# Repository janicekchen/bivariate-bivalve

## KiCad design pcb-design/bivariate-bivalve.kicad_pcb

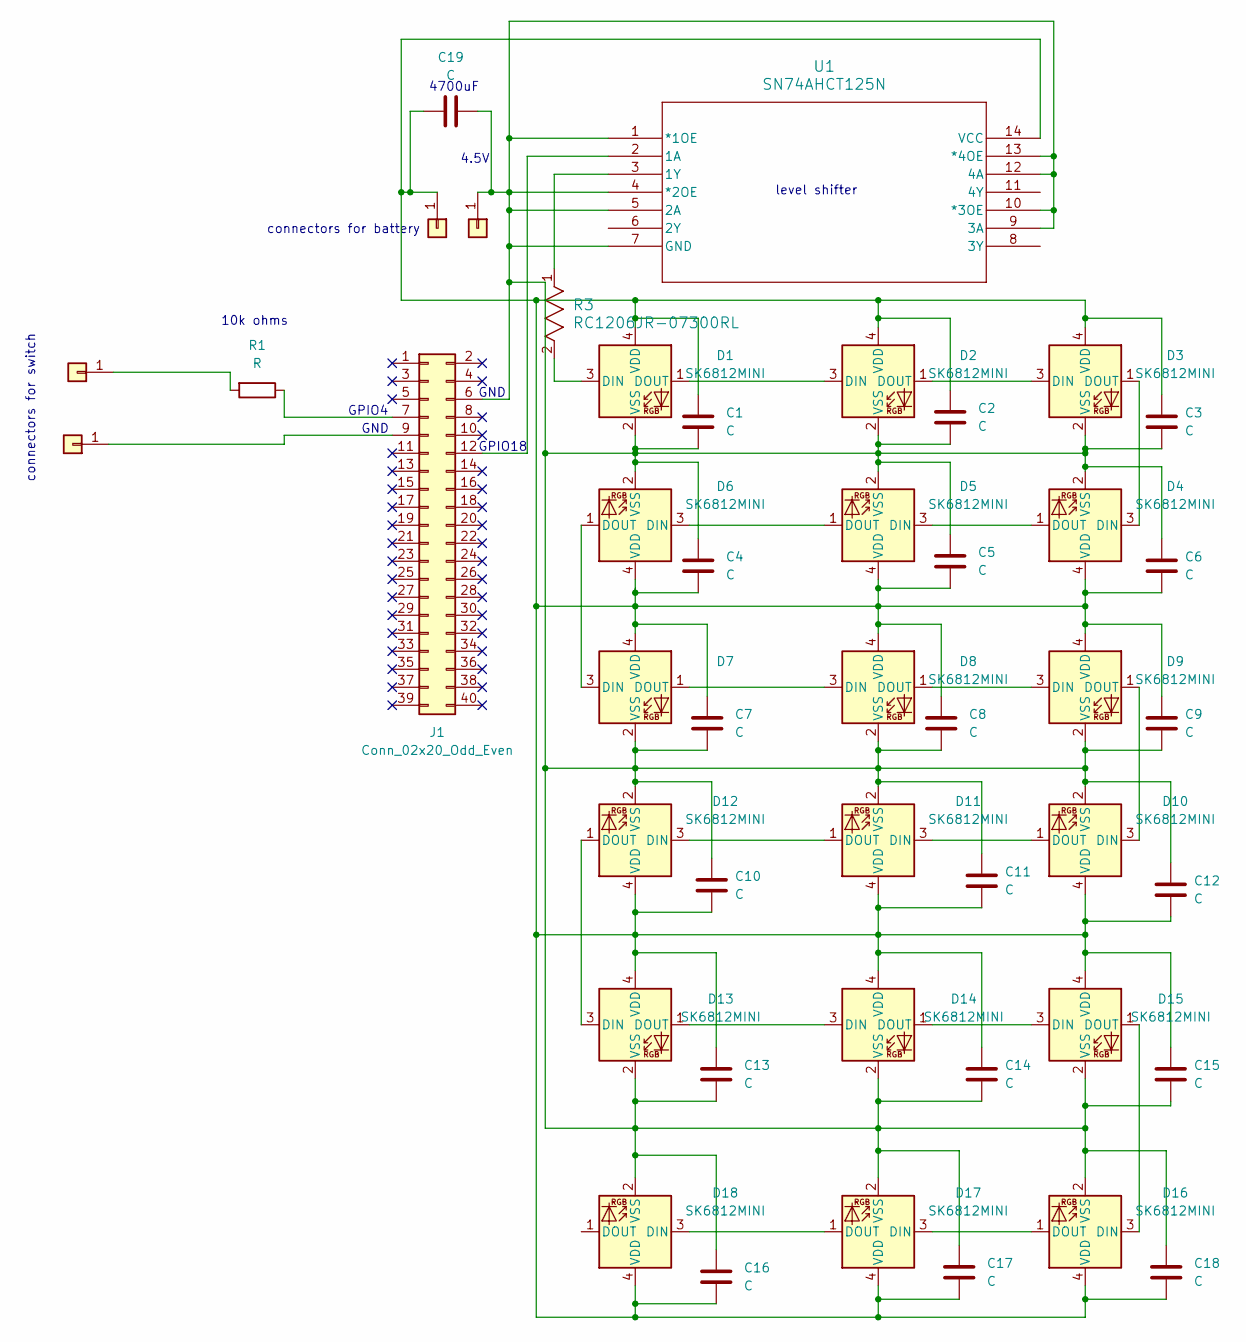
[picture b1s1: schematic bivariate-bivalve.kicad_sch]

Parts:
C1, C2, C3, C4, C5, C6, C7, C8, C9, C10, C11, C12, C13, C14, C15, C16, C17, C18: C; CAPC1608X100N
C19: C; C_Radial_D10.0mm_H16.0mm_P5.00mm
D1, D2, D3, D4, D5, D6, D7, D8, D9, D10, D11, D12, D13, D14, D15, D16, D17, D18: SK6812MINI; LED_SK6812MINI_PLCC4_3.5x3.5mm_P1.75mm
J1: Conn_02x20_Odd_Even; PinSocket_2x20_P2.54mm_Vertical
J2, J3, J4, J5: Conn_01x01; SolderWire-0.5sqmm_1x01_D0.9mm_OD2.1mm
R1: R; R_Axial_DIN0207_L6.3mm_D2.5mm_P7.62mm_Horizontal
R3: RC1206JR-07300RL; RC1206N_YAG
U1: SN74AHCT125N; N14

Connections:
unnamed: D1.3 (DIN), R3.2
unnamed: D1.1 (DOUT), D2.3 (DIN)
unnamed: C1.1, C2.1, C3.1, C4.2, C5.2, C6.1, C7.1, C8.1, C9.1, C10.2, C11.2, C12.2, C13.1, C14.1, C15.1, C16.2, C17.2, C18.2, C19.1, D1.4 (VDD), D2.4 (VDD), D3.4 (VDD), D4.4 (VDD), D5.4 (VDD), D6.4 (VDD), D7.4 (VDD), D8.4 (VDD), D9.4 (VDD), D10.4 (VDD), D11.4 (VDD), D12.4 (VDD), D13.4 (VDD), D14.4 (VDD), D15.4 (VDD), D16.4 (VDD), D17.4 (VDD), D18.4 (VDD), J4.1, U1.14 (VCC)
unnamed: C1.2, C2.2, C3.2, C4.1, C5.1, C6.2, C7.2, C8.2, C9.2, C10.1, C11.1, C12.1, C13.2, C14.2, C15.2, C16.1, C17.1, C18.1, C19.2, D1.2 (VSS), D2.2 (VSS), D3.2 (VSS), D4.2 (VSS), D5.2 (VSS), D6.2 (VSS), D7.2 (VSS), D8.2 (VSS), D9.2 (VSS), D10.2 (VSS), D11.2 (VSS), D12.2 (VSS), D13.2 (VSS), D14.2 (VSS), D15.2 (VSS), D16.2 (VSS), D17.2 (VSS), D18.2 (VSS), J1.6, J5.1, U1.1 (*1OE), U1.4 (*2OE), U1.5 (2A), U1.7 (GND), U1.9 (3A), U1.10 (*3OE), U1.12 (4A), U1.13 (*4OE)
unnamed: D2.1 (DOUT), D3.3 (DIN)
unnamed: D3.1 (DOUT), D4.3 (DIN)
unnamed: D4.1 (DOUT), D5.3 (DIN)
unnamed: D5.1 (DOUT), D6.3 (DIN)
unnamed: D6.1 (DOUT), D7.3 (DIN)
unnamed: D7.1 (DOUT), D8.3 (DIN)
unnamed: D8.1 (DOUT), D9.3 (DIN)
unnamed: D9.1 (DOUT), D10.3 (DIN)
unnamed: D10.1 (DOUT), D11.3 (DIN)
unnamed: D11.1 (DOUT), D12.3 (DIN)
unnamed: D12.1 (DOUT), D13.3 (DIN)
unnamed: D13.1 (DOUT), D14.3 (DIN)
unnamed: D14.1 (DOUT), D15.3 (DIN)
unnamed: D15.1 (DOUT), D16.3 (DIN)
unnamed: D16.1 (DOUT), D17.3 (DIN)
unnamed: D17.1 (DOUT), D18.3 (DIN)
unnamed: J1.7, R1.1
unnamed: J1.9, J3.1
unnamed: J1.12, U1.2 (1A)
unnamed: J2.1, R1.2
unnamed: R3.1, U1.3 (1Y)

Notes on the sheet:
4700uF
GPIO4
10k ohms
connectors for switch
connectors for battery
GND
4.5V
level shifter
GPIO18

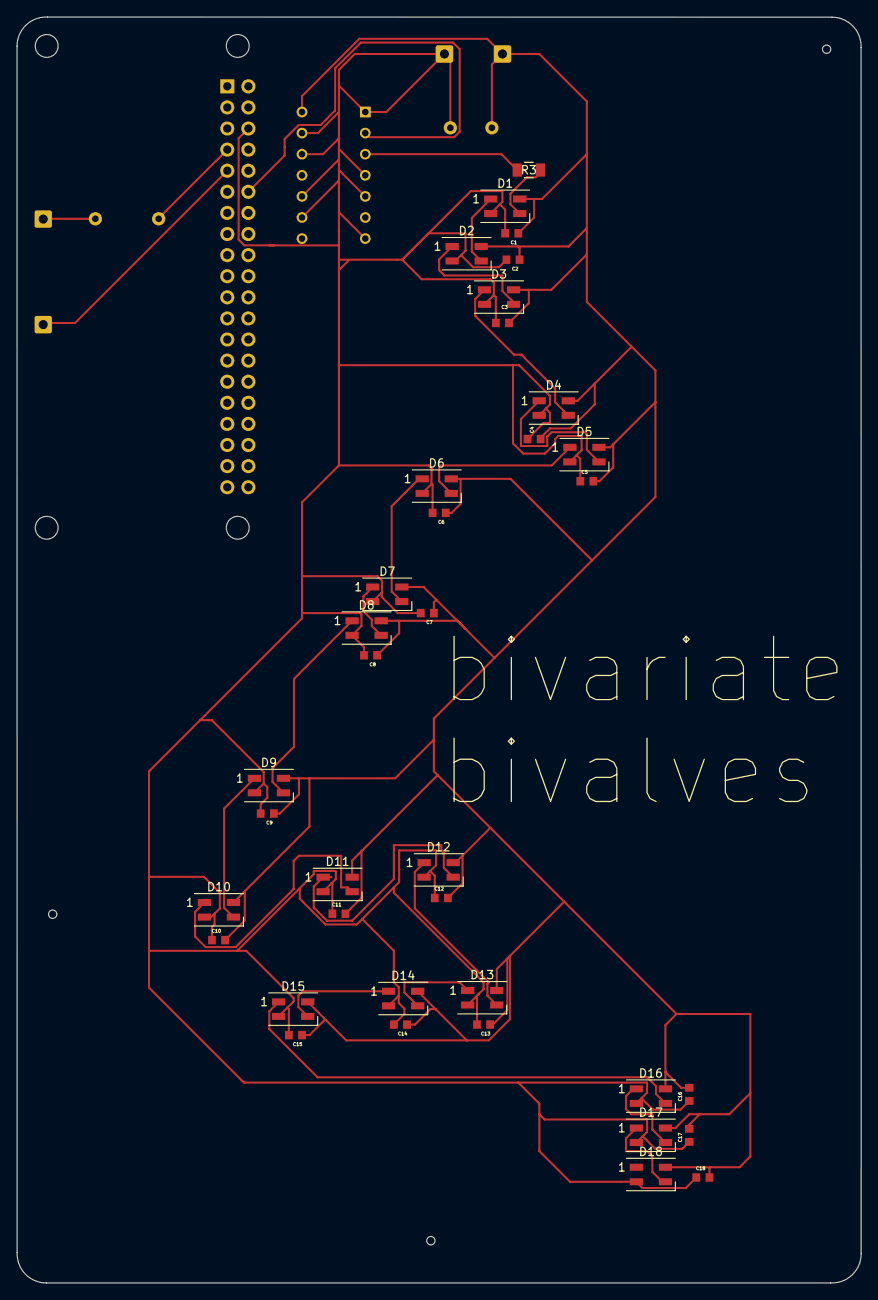
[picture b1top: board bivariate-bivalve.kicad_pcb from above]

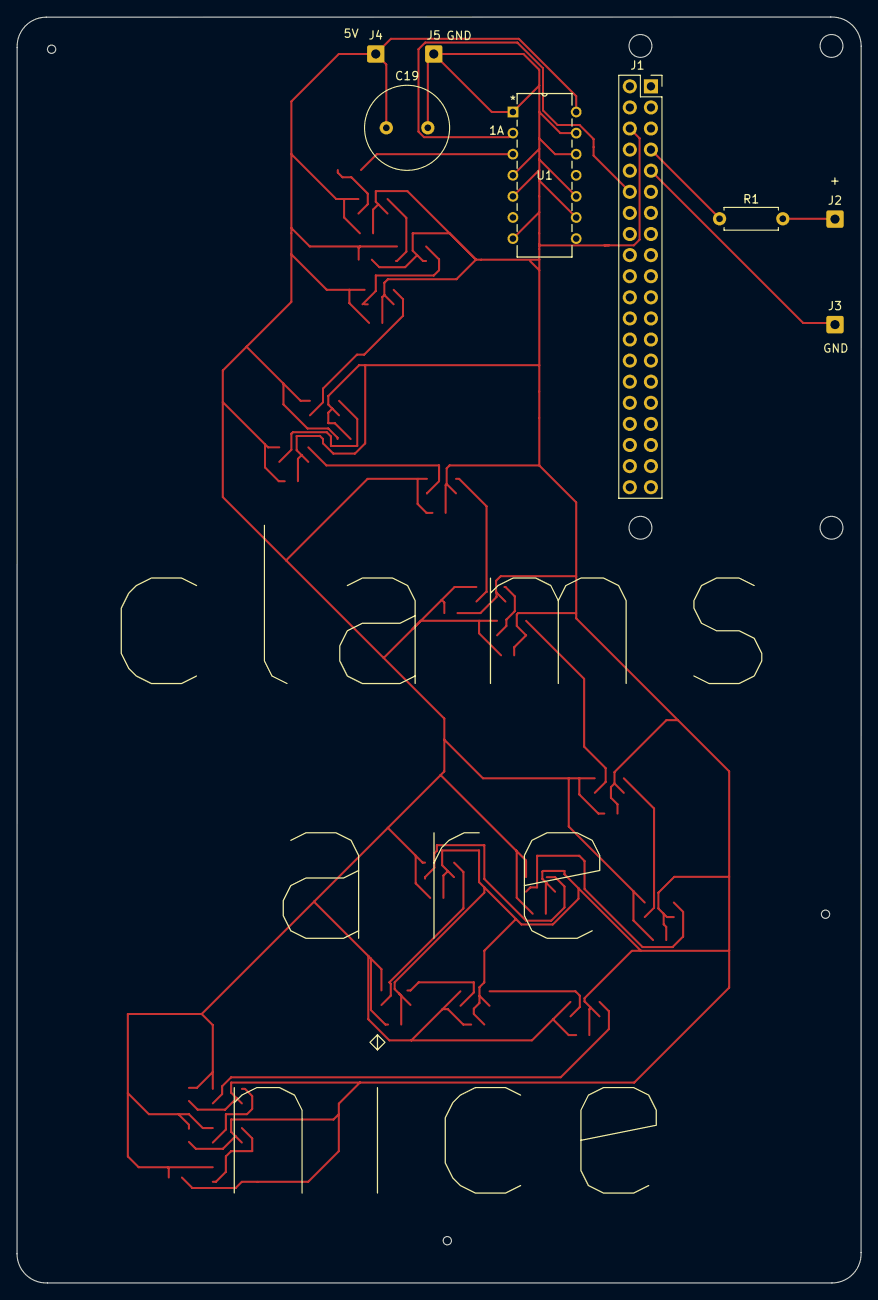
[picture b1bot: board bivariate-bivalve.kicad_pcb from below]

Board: 2 copper layers, 101.6 x 152.4 mm, 45 parts (8 on the bottom side), 25 nets.

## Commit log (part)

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2024-03-15 GH ACTION bivalve-update Fri Mar 15 11:11:40 UTC 2024
2024-03-18 GH ACTION bivalve-update Mon Mar 18 11:12:30 UTC 2024
2024-03-20 GH ACTION bivalve-update Wed Mar 20 11:12:46 UTC 2024
2024-03-22 GH ACTION bivalve-update Fri Mar 22 11:11:44 UTC 2024
2024-03-24 GH ACTION bivalve-update Sun Mar 24 11:12:18 UTC 2024
2024-03-26 GH ACTION bivalve-update Tue Mar 26 11:12:12 UTC 2024
2024-03-29 GH ACTION bivalve-update Fri Mar 29 11:12:24 UTC 2024
2024-04-01 GH ACTION bivalve-update Mon Apr 1 11:12:45 UTC 2024
2024-04-03 GH ACTION bivalve-update Wed Apr 3 11:12:10 UTC 2024
2024-04-05 GH ACTION bivalve-update Fri Apr 5 11:12:58 UTC 2024
2024-04-07 GH ACTION bivalve-update Sun Apr 7 11:12:00 UTC 2024
2024-04-10 GH ACTION bivalve-update Wed Apr 10 11:13:14 UTC 2024
2024-04-12 GH ACTION bivalve-update Fri Apr 12 11:13:01 UTC 2024
2024-04-15 GH ACTION bivalve-update Mon Apr 15 11:13:53 UTC 2024
2024-04-17 GH ACTION bivalve-update Wed Apr 17 11:12:45 UTC 2024
2024-04-19 GH ACTION bivalve-update Fri Apr 19 11:12:25 UTC 2024
2024-04-22 GH ACTION bivalve-update Mon Apr 22 11:12:24 UTC 2024
2024-04-24 GH ACTION bivalve-update Wed Apr 24 11:12:08 UTC 2024
2024-04-26 GH ACTION bivalve-update Fri Apr 26 11:11:43 UTC 2024
2024-04-28 GH ACTION bivalve-update Sun Apr 28 11:10:55 UTC 2024
2024-04-30 GH ACTION bivalve-update Tue Apr 30 11:11:48 UTC 2024
2024-05-02 GH ACTION bivalve-update Thu May 2 11:11:50 UTC 2024
2024-05-05 GH ACTION bivalve-update Sun May 5 11:11:33 UTC 2024
2024-05-07 GH ACTION bivalve-update Tue May 7 11:12:25 UTC 2024
2024-05-10 GH ACTION bivalve-update Fri May 10 11:11:37 UTC 2024
2024-05-13 GH ACTION bivalve-update Mon May 13 11:11:16 UTC 2024
2024-05-15 GH ACTION bivalve-update Wed May 15 11:11:15 UTC 2024
2024-05-17 GH ACTION bivalve-update Fri May 17 11:11:14 UTC 2024
2024-05-20 GH ACTION bivalve-update Mon May 20 11:11:35 UTC 2024
2024-05-22 GH ACTION bivalve-update Wed May 22 11:11:26 UTC 2024
2024-05-24 GH ACTION bivalve-update Fri May 24 11:11:52 UTC 2024
2024-05-26 GH ACTION bivalve-update Sun May 26 11:11:26 UTC 2024
2024-05-29 GH ACTION bivalve-update Wed May 29 11:12:15 UTC 2024
2024-05-31 GH ACTION bivalve-update Fri May 31 11:12:09 UTC 2024
2024-06-04 GH ACTION bivalve-update Tue Jun 4 11:12:30 UTC 2024
2024-06-06 GH ACTION bivalve-update Thu Jun 6 11:12:10 UTC 2024
2024-06-08 GH ACTION bivalve-update Sat Jun 8 11:11:54 UTC 2024
2024-06-10 GH ACTION bivalve-update Mon Jun 10 11:12:24 UTC 2024
2024-06-12 GH ACTION bivalve-update Wed Jun 12 11:12:22 UTC 2024
2024-06-14 GH ACTION bivalve-update Fri Jun 14 11:12:08 UTC 2024
2024-06-16 GH ACTION bivalve-update Sun Jun 16 11:12:15 UTC 2024
2024-06-18 GH ACTION bivalve-update Tue Jun 18 11:12:13 UTC 2024
2024-06-20 GH ACTION bivalve-update Thu Jun 20 11:11:48 UTC 2024
2024-06-23 GH ACTION bivalve-update Sun Jun 23 11:11:39 UTC 2024
2024-06-25 GH ACTION bivalve-update Tue Jun 25 11:12:03 UTC 2024
2024-06-27 GH ACTION bivalve-update Thu Jun 27 11:11:55 UTC 2024
2024-06-30 GH ACTION bivalve-update Sun Jun 30 11:11:52 UTC 2024
2024-07-02 update led code
2024-07-02 change tide from character to numeric
2024-07-02 GH ACTION bivalve-update Tue Jul 2 11:09:12 UTC 2024
2024-07-04 GH ACTION bivalve-update Thu Jul 4 11:10:04 UTC 2024
2024-07-06 GH ACTION bivalve-update Sat Jul 6 11:09:23 UTC 2024
2024-07-08 GH ACTION bivalve-update Mon Jul 8 11:09:37 UTC 2024
2024-07-11 GH ACTION bivalve-update Thu Jul 11 11:09:10 UTC 2024
2024-07-13 GH ACTION bivalve-update Sat Jul 13 11:09:00 UTC 2024
2024-07-15 GH ACTION bivalve-update Mon Jul 15 11:09:18 UTC 2024
2024-07-17 GH ACTION bivalve-update Wed Jul 17 11:09:22 UTC 2024
2024-07-19 GH ACTION bivalve-update Fri Jul 19 11:09:34 UTC 2024
2024-07-21 GH ACTION bivalve-update Sun Jul 21 11:09:05 UTC 2024
2024-07-23 GH ACTION bivalve-update Tue Jul 23 11:09:47 UTC 2024
2024-07-25 GH ACTION bivalve-update Thu Jul 25 11:09:17 UTC 2024
2024-07-28 GH ACTION bivalve-update Sun Jul 28 11:09:05 UTC 2024
2024-07-30 GH ACTION bivalve-update Tue Jul 30 11:10:30 UTC 2024
2024-08-01 GH ACTION bivalve-update Thu Aug 1 11:09:26 UTC 2024
2024-08-04 GH ACTION bivalve-update Sun Aug 4 11:09:08 UTC 2024
2024-08-06 GH ACTION bivalve-update Tue Aug 6 11:09:12 UTC 2024
2024-08-27 GH ACTION bivalve-update Tue Aug 27 11:09:23 UTC 2024
2024-08-29 GH ACTION bivalve-update Thu Aug 29 11:09:06 UTC 2024
2024-08-31 GH ACTION bivalve-update Sat Aug 31 11:08:15 UTC 2024
2024-09-02 GH ACTION bivalve-update Mon Sep 2 11:08:53 UTC 2024
2024-09-04 GH ACTION bivalve-update Wed Sep 4 11:08:18 UTC 2024
2024-09-06 GH ACTION bivalve-update Fri Sep 6 11:08:36 UTC 2024
2024-09-08 GH ACTION bivalve-update Sun Sep 8 11:08:31 UTC 2024
2024-09-10 GH ACTION bivalve-update Tue Sep 10 11:08:32 UTC 2024
2024-09-13 GH ACTION bivalve-update Fri Sep 13 11:08:55 UTC 2024
2024-09-15 GH ACTION bivalve-update Sun Sep 15 11:08:17 UTC 2024
2024-09-17 GH ACTION bivalve-update Tue Sep 17 11:08:30 UTC 2024
2024-09-20 GH ACTION bivalve-update Fri Sep 20 11:08:37 UTC 2024
2024-09-22 GH ACTION bivalve-update Sun Sep 22 11:08:41 UTC 2024
2024-09-24 GH ACTION bivalve-update Tue Sep 24 11:08:30 UTC 2024
2024-09-26 GH ACTION bivalve-update Thu Sep 26 11:08:45 UTC 2024
2024-09-28 GH ACTION bivalve-update Sat Sep 28 11:08:58 UTC 2024
2024-09-30 GH ACTION bivalve-update Mon Sep 30 11:08:44 UTC 2024
2024-10-02 GH ACTION bivalve-update Wed Oct 2 11:09:01 UTC 2024
2024-10-04 GH ACTION bivalve-update Fri Oct 4 11:09:19 UTC 2024
2024-10-07 GH ACTION bivalve-update Mon Oct 7 11:09:06 UTC 2024
2024-10-09 GH ACTION bivalve-update Wed Oct 9 11:09:02 UTC 2024
2024-10-12 GH ACTION bivalve-update Sat Oct 12 11:08:58 UTC 2024
2024-10-15 GH ACTION bivalve-update Tue Oct 15 11:08:39 UTC 2024
2024-10-17 GH ACTION bivalve-update Thu Oct 17 11:09:24 UTC 2024
2024-10-19 GH ACTION bivalve-update Sat Oct 19 11:08:39 UTC 2024
2024-10-21 GH ACTION bivalve-update Mon Oct 21 11:08:57 UTC 2024
2024-10-23 GH ACTION bivalve-update Wed Oct 23 11:08:43 UTC 2024
2024-10-25 GH ACTION bivalve-update Fri Oct 25 11:08:56 UTC 2024
2024-10-27 GH ACTION bivalve-update Sun Oct 27 11:08:26 UTC 2024
2024-10-30 GH ACTION bivalve-update Wed Oct 30 11:09:30 UTC 2024
2024-11-01 GH ACTION bivalve-update Fri Nov 1 11:08:38 UTC 2024
2024-11-03 GH ACTION bivalve-update Sun Nov 3 11:10:31 UTC 2024
2024-11-05 GH ACTION bivalve-update Tue Nov 5 11:09:07 UTC 2024
2024-11-07 GH ACTION bivalve-update Thu Nov 7 11:08:57 UTC 2024
2024-11-09 GH ACTION bivalve-update Sat Nov 9 11:08:30 UTC 2024
2024-11-11 GH ACTION bivalve-update Mon Nov 11 11:09:03 UTC 2024
2024-11-13 GH ACTION bivalve-update Wed Nov 13 11:08:42 UTC 2024
2024-11-15 GH ACTION bivalve-update Fri Nov 15 11:08:56 UTC 2024
2024-11-17 GH ACTION bivalve-update Sun Nov 17 11:08:35 UTC 2024
2024-11-19 GH ACTION bivalve-update Tue Nov 19 11:09:02 UTC 2024
2024-11-25 GH ACTION bivalve-update Mon Nov 25 11:08:58 UTC 2024
2024-11-27 GH ACTION bivalve-update Wed Nov 27 11:08:53 UTC 2024
2024-11-29 GH ACTION bivalve-update Fri Nov 29 11:09:05 UTC 2024
2024-12-01 GH ACTION bivalve-update Sun Dec 1 11:08:58 UTC 2024
2024-12-03 GH ACTION bivalve-update Tue Dec 3 11:08:56 UTC 2024
2024-12-05 GH ACTION bivalve-update Thu Dec 5 11:08:56 UTC 2024
2024-12-07 GH ACTION bivalve-update Sat Dec 7 11:08:44 UTC 2024
2024-12-10 GH ACTION bivalve-update Tue Dec 10 11:09:07 UTC 2024
2024-12-12 GH ACTION bivalve-update Thu Dec 12 11:08:52 UTC 2024
2024-12-14 GH ACTION bivalve-update Sat Dec 14 11:08:56 UTC 2024
2024-12-16 GH ACTION bivalve-update Mon Dec 16 11:08:53 UTC 2024
2024-12-19 GH ACTION bivalve-update Thu Dec 19 11:08:56 UTC 2024
2024-12-21 GH ACTION bivalve-update Sat Dec 21 11:08:19 UTC 2024
2024-12-23 GH ACTION bivalve-update Mon Dec 23 11:08:41 UTC 2024
2024-12-25 GH ACTION bivalve-update Wed Dec 25 11:08:31 UTC 2024
2024-12-27 GH ACTION bivalve-update Fri Dec 27 11:08:38 UTC 2024
2024-12-29 GH ACTION bivalve-update Sun Dec 29 11:08:17 UTC 2024
2024-12-31 GH ACTION bivalve-update Tue Dec 31 11:08:41 UTC 2024
2025-01-02 GH ACTION bivalve-update Thu Jan 2 11:08:50 UTC 2025
2025-01-04 GH ACTION bivalve-update Sat Jan 4 11:08:32 UTC 2025
2025-01-06 GH ACTION bivalve-update Mon Jan 6 11:08:42 UTC 2025
2025-01-09 GH ACTION bivalve-update Thu Jan 9 11:09:46 UTC 2025
2025-01-11 GH ACTION bivalve-update Sat Jan 11 11:08:43 UTC 2025
2025-01-13 GH ACTION bivalve-update Mon Jan 13 11:09:07 UTC 2025
2025-01-15 GH ACTION bivalve-update Wed Jan 15 11:09:02 UTC 2025
2025-01-18 GH ACTION bivalve-update Sat Jan 18 11:08:37 UTC 2025
2025-01-20 GH ACTION bivalve-update Mon Jan 20 11:09:09 UTC 2025
2025-01-22 GH ACTION bivalve-update Wed Jan 22 11:08:47 UTC 2025
2025-01-24 GH ACTION bivalve-update Fri Jan 24 11:08:42 UTC 2025
2025-01-26 GH ACTION bivalve-update Sun Jan 26 11:08:25 UTC 2025
2025-01-28 GH ACTION bivalve-update Tue Jan 28 11:09:29 UTC 2025
2025-01-30 GH ACTION bivalve-update Thu Jan 30 11:08:42 UTC 2025
2025-02-02 GH ACTION bivalve-update Sun Feb 2 11:08:35 UTC 2025
2025-02-04 GH ACTION bivalve-update Tue Feb 4 11:08:43 UTC 2025
2025-02-06 GH ACTION bivalve-update Thu Feb 6 11:09:18 UTC 2025
2025-02-08 GH ACTION bivalve-update Sat Feb 8 11:08:19 UTC 2025
2025-02-10 GH ACTION bivalve-update Mon Feb 10 11:09:20 UTC 2025
2025-02-12 GH ACTION bivalve-update Wed Feb 12 11:08:45 UTC 2025
2025-02-15 GH ACTION bivalve-update Sat Feb 15 11:08:31 UTC 2025
2025-02-17 GH ACTION bivalve-update Mon Feb 17 11:09:01 UTC 2025
2025-02-19 GH ACTION bivalve-update Wed Feb 19 11:09:03 UTC 2025
2025-02-21 GH ACTION bivalve-update Fri Feb 21 11:08:58 UTC 2025
2025-02-24 GH ACTION bivalve-update Mon Feb 24 11:08:44 UTC 2025
2025-02-26 GH ACTION bivalve-update Wed Feb 26 11:08:52 UTC 2025
2025-02-28 GH ACTION bivalve-update Fri Feb 28 11:08:48 UTC 2025
2025-03-02 GH ACTION bivalve-update Sun Mar 2 11:08:44 UTC 2025
2025-03-04 GH ACTION bivalve-update Tue Mar 4 11:08:46 UTC 2025
2025-03-06 GH ACTION bivalve-update Thu Mar 6 11:09:04 UTC 2025
2025-03-08 GH ACTION bivalve-update Sat Mar 8 11:09:12 UTC 2025
2025-03-10 GH ACTION bivalve-update Mon Mar 10 11:08:46 UTC 2025
2025-03-12 GH ACTION bivalve-update Wed Mar 12 11:09:06 UTC 2025
2025-03-15 GH ACTION bivalve-update Sat Mar 15 11:08:38 UTC 2025
2025-03-17 GH ACTION bivalve-update Mon Mar 17 11:09:11 UTC 2025
2025-03-20 GH ACTION bivalve-update Thu Mar 20 11:08:50 UTC 2025
2025-03-22 GH ACTION bivalve-update Sat Mar 22 11:08:53 UTC 2025
2025-03-24 GH ACTION bivalve-update Mon Mar 24 11:09:10 UTC 2025
2025-03-26 GH ACTION bivalve-update Wed Mar 26 11:09:03 UTC 2025
2025-03-28 GH ACTION bivalve-update Fri Mar 28 11:08:58 UTC 2025
2025-03-30 GH ACTION bivalve-update Sun Mar 30 11:08:57 UTC 2025
2025-04-01 GH ACTION bivalve-update Tue Apr 1 11:08:39 UTC 2025
2025-04-03 GH ACTION bivalve-update Thu Apr 3 11:08:59 UTC 2025
2025-04-06 GH ACTION bivalve-update Sun Apr 6 11:08:45 UTC 2025
2025-04-08 GH ACTION bivalve-update Tue Apr 8 11:08:42 UTC 2025
2025-04-11 GH ACTION bivalve-update Fri Apr 11 11:08:41 UTC 2025
2025-04-13 GH ACTION bivalve-update Sun Apr 13 11:08:26 UTC 2025
2025-04-15 GH ACTION bivalve-update Tue Apr 15 11:08:45 UTC 2025
2025-04-17 GH ACTION bivalve-update Thu Apr 17 11:08:34 UTC 2025
2025-04-19 GH ACTION bivalve-update Sat Apr 19 11:08:58 UTC 2025
2025-04-21 GH ACTION bivalve-update Mon Apr 21 11:08:42 UTC 2025
2025-04-23 GH ACTION bivalve-update Wed Apr 23 11:08:40 UTC 2025
2025-04-25 GH ACTION bivalve-update Fri Apr 25 11:08:35 UTC 2025
2025-04-27 GH ACTION bivalve-update Sun Apr 27 11:08:49 UTC 2025
2025-04-29 GH ACTION bivalve-update Tue Apr 29 11:08:48 UTC 2025
2025-05-01 GH ACTION bivalve-update Thu May 1 11:09:00 UTC 2025
2025-05-04 GH ACTION bivalve-update Sun May 4 11:08:30 UTC 2025
2025-05-06 GH ACTION bivalve-update Tue May 6 11:08:50 UTC 2025
2025-05-08 GH ACTION bivalve-update Thu May 8 11:09:16 UTC 2025
2025-05-10 GH ACTION bivalve-update Sat May 10 11:09:10 UTC 2025
2025-05-12 GH ACTION bivalve-update Mon May 12 11:08:56 UTC 2025
2025-05-14 GH ACTION bivalve-update Wed May 14 11:09:07 UTC 2025
2025-05-16 GH ACTION bivalve-update Fri May 16 11:08:44 UTC 2025
2025-05-18 GH ACTION bivalve-update Sun May 18 11:08:28 UTC 2025
2025-05-20 GH ACTION bivalve-update Tue May 20 11:08:49 UTC 2025
